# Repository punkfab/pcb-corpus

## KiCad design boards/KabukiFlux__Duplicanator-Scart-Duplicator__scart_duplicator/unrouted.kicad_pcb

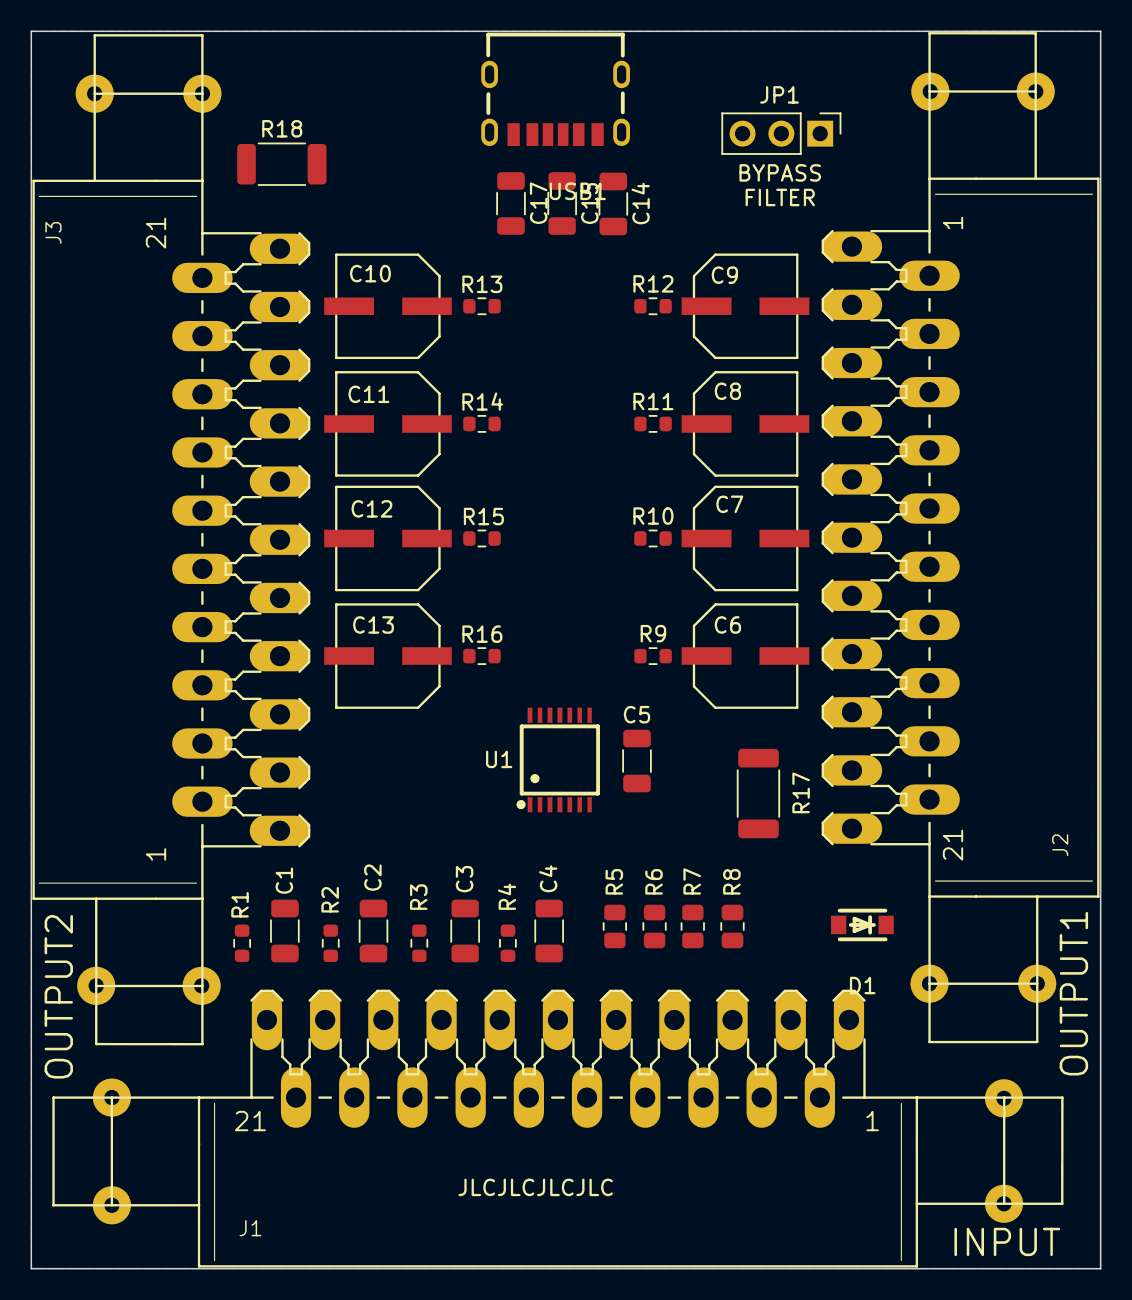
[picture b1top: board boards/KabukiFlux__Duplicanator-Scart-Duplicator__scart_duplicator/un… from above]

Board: 2 copper layers, 70.0 x 81.0 mm, 42 parts (1 on the bottom side), 38 nets, no tracks yet.

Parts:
C1, C2, C3, C4, C5, C17: 0.1u; C_1206_3216Metric
C6, C7, C8, C9, C10, C11, C12, C13: 330u; CAP-SMD_BD6.3-L6.6-W6.6-LS7.2-R-RD
C14: 10n; C_1206_3216Metric
C15: 10u; C_1206_3216Metric
D1: SOD4007; SOD-123F_L2.8-W1.8-LS3.7-RD
G1: LOGO; LogoKabuki
J1: INPUT; SCART-F_solder_pads
J2: OUTPUT1; SCART-F_solder_pads
J3: OUTPUT2; SCART-F_solder_pads
JP1: FILTER_BYPASS; PinHeader_1x03_P2.54mm_Vertical
R1, R2, R3, R4, R9, R10, R11, R12, R13, R14, R15, R16: 75; R_0603_1608Metric
R5, R6, R7, R8: 5.36M; R_0805_2012Metric
R17, R18: 180; R_2010_5025Metric
U1: THS7374IPWR; TSSOP-14_L5.0-W4.4-P0.65-LS6.5-BL
USB1: USB-312; USB-C-SMD_10P-P1.00-L6.8-W8.9

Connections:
+5V: C5.1, C14.1, C15.1, C17.1, JP1.3 (B), R5.2, R6.2, R7.2, R8.2, R17.2, R18.2, U1.10 (VS+), USB1.2 (B9_VBUS), USB1.5 (A9_VBUS)
/AUDIO_GND: J1.4, J2.4, J3.4
/AUDIO_LEFT: J1.6, J2.3, J3.3
/AUDIO_RIGHT: J1.2, J2.1, J3.1
/B_IN: C4.1, J1.7, R4.1
/B_OUT1: C9.2, J2.7
/B_OUT2: C13.2, J3.7
/CSYNC_IN: C1.1, J1.20, R1.1
/CSYNC_OUT1: C6.2, J2.19
/CSYNC_OUT2: C10.2, J3.19
/G_IN: C3.1, J1.11, R3.1
/G_OUT1: C8.2, J2.11
/G_OUT2: C12.2, J3.11
/R_IN: C2.1, J1.15, R2.1
/R_OUT1: C7.2, J2.15
/R_OUT2: C11.2, J3.15
/SWITCHING: D1.1 (C), J2.8, J3.8
GND: C5.2, C14.2, C15.2, C17.2, J1.5, J1.9, J1.13, J1.17, J1.18, J1.21, J2.5, J2.9, J2.13, J2.17, J2.18, J2.21, J3.5, J3.9, J3.13, J3.17, J3.18, J3.21, JP1.1 (A), R1.2, R2.2, R3.2, R4.2, U1.5 (GND), U1.6 (DISABLE), USB1.0, USB1.1 (B12_GND), USB1.6 (A12_GND)
unnamed: C6.1, R9.2
unnamed: C7.1, R10.2
unnamed: C8.1, R11.2
unnamed: C9.1, R12.2
unnamed: C10.1, R13.2
unnamed: C11.1, R14.2
unnamed: C12.1, R15.2
unnamed: C13.1, R16.2
unnamed: D1.2 (A), J1.8
unnamed: J2.16, R17.1
unnamed: J3.16, R18.1
unnamed: JP1.2 (C), U1.9 (BYPASS)
unnamed: C1.2, R5.1, U1.1 (CH1IN)
unnamed: R9.1, R13.1, U1.14 (CH1OUT)
unnamed: C2.2, R6.1, U1.2 (CH2IN)
unnamed: R10.1, R14.1, U1.13 (CH2OUT)
unnamed: C3.2, R7.1, U1.3 (CH3IN)
unnamed: R11.1, R15.1, U1.12 (CH3OUT)
unnamed: C4.2, R8.1, U1.4 (CH4IN)
unnamed: R12.1, R16.1, U1.11 (CH4OUT)

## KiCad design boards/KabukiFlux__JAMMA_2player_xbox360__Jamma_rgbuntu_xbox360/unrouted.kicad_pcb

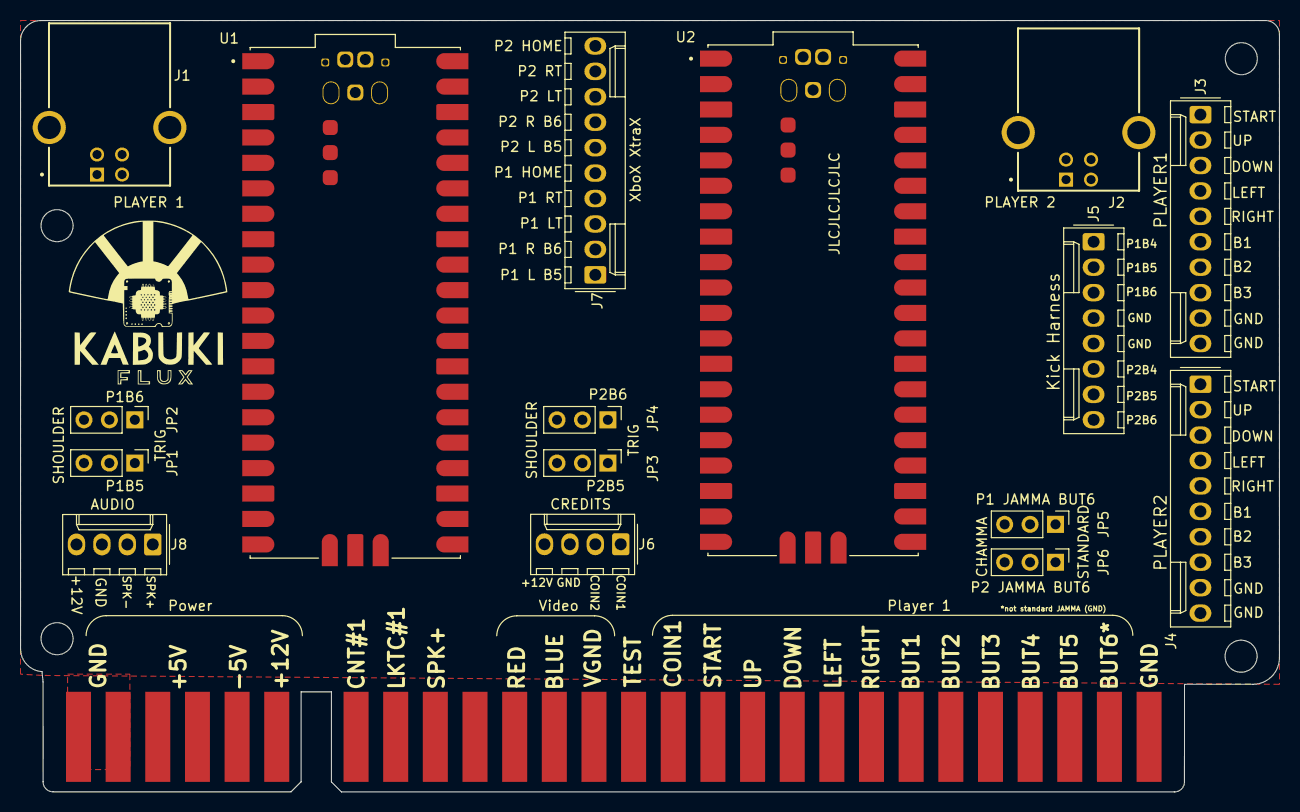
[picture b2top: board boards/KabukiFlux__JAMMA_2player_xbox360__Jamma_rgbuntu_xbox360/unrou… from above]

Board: 2 copper layers, 125.7 x 77.0 mm, 22 parts (0 on the bottom side), 47 nets, no tracks yet.

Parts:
G1: LOGO; LogoKabuki_18mm
HOLE1, HOLE2, HOLE3, HOLE4: MountingHole_3.2mm_M3
J1: USB-B PICO1; USB-B
J2: USB-B PICO2; USB-B
J3: PLAYER1; Molex_KK-254_AE-6410-10A_1x10_P2.54mm_Vertical
J4: PLAYER2; Molex_KK-254_AE-6410-10A_1x10_P2.54mm_Vertical
J5: Kick Harness; Molex_KK-254_AE-6410-08A_1x08_P2.54mm_Vertical
J6: CREDITS; Molex_KK-254_AE-6410-04A_1x04_P2.54mm_Vertical
J7: XboX XtraX; Molex_KK-254_AE-6410-10A_1x10_P2.54mm_Vertical
J8: AUDIO; Molex_KK-254_AE-6410-04A_1x04_P2.54mm_Vertical
J9: JAMMA_edge_conn; JAMMA_edge
JP1: P1_B5_SELECTOR; PinHeader_1x03_P2.54mm_Vertical
JP2: P1_B6_SELECTOR; PinHeader_1x03_P2.54mm_Vertical
JP3: P2_B5_SELECTOR; PinHeader_1x03_P2.54mm_Vertical
JP4: P2_B6_SELECTOR; PinHeader_1x03_P2.54mm_Vertical
JP5: P1 JAMMA BUT6; PinHeader_1x03_P2.54mm_Vertical
JP6: P2 JAMMA BUT6; PinHeader_1x03_P2.54mm_Vertical
U1, U2: pi_pico; pi-pico

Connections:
/+12V: J6.4, J8.4, J9.6 (+12V), J9.F (+12V)
/GND: J1.4 (GND), J2.4 (GND), J3.9, J3.10, J4.9, J4.10, J5.4, J5.5, J6.3, J8.3, J9.1 (GND), J9.2 (GND), J9.28 (GND), J9.A (GND), J9.B (GND), J9.f (GND), JP5.1 (A), JP6.1 (A), U1.3 (GND), U1.8 (GND), U1.13 (GND), U1.18 (GND), U1.23 (GND), U1.28 (GND), U1.38 (GND), U1.D2 (GND), U1.TP1 (TP1_GND), U2.3 (GND), U2.8 (GND), U2.13 (GND), U2.18 (GND), U2.23 (GND), U2.28 (GND), U2.38 (GND), U2.D2 (GND), U2.TP1 (TP1_GND)
/P1_A_B1: J3.6, J9.22 (Player_1_Button_1), U1.9 (GP6)
/P1_B5: J5.2, J9.26 (Unused), JP1.2 (C)
/P1_B6: J5.3, JP2.2 (C), JP5.3 (B)
/P1_B_B2: J3.7, J9.23 (Player_1_Button_2), U1.10 (GP7)
/P1_COIN_B7: J6.1, J9.16 (Coin_1), U1.21 (GP16)
/P1_DPAD_DOWN: J3.3, J9.19 (Player_1_Down), U1.5 (GP3)
/P1_DPAD_LEFT: J3.4, J9.20 (Player_1_Left), U1.7 (GP5)
/P1_DPAD_RIGHT: J3.5, J9.21 (Player_1_Right), U1.6 (GP4)
/P1_DPAD_UP: J3.2, J9.18 (Player_1_Up), U1.4 (GP2)
/P1_HOME: J7.5, U1.26 (GP20)
/P1_JAMMA_B6_GND: J9.27 (GND), JP5.2 (C)
/P1_LT: J7.3, JP1.1 (A), U1.12 (GP9)
/P1_L_B5: J7.1, JP1.3 (B), U1.17 (GP13)
/P1_RT: J7.4, JP2.1 (A), U1.11 (GP8)
/P1_R_B6: J7.2, JP2.3 (B), U1.16 (GP12)
/P1_START_B8: J3.1, J9.17 (Player_1_Start), U1.22 (GP17)
/P1_X_B3: J3.8, J9.24 (Player_1_Button_3), U1.14 (GP10)
/P1_Y_B4: J5.1, J9.25 (Player_1_Button_4), U1.15 (GP11)
/P2_A_B1: J4.6, J9.Z (Player_2_Button_1), U2.9 (GP6)
/P2_B5: J5.7, J9.d (Unused), JP3.2 (C)
/P2_B6: J5.8, JP4.2 (C), JP6.3 (B)
/P2_B_B2: J4.7, J9.a (Player_2_Button_2), U2.10 (GP7)
/P2_COIN_B7: J6.2, J9.T (Coin_2), U2.21 (GP16)
/P2_DPAD_DOWN: J4.3, J9.W (Player_2_Down), U2.5 (GP3)
/P2_DPAD_LEFT: J4.4, J9.X (Player_2_Left), U2.7 (GP5)
/P2_DPAD_RIGHT: J4.5, J9.Y (Player_2_Right), U2.6 (GP4)
/P2_DPAD_UP: J4.2, J9.V (Player_2_Up), U2.4 (GP2)
/P2_HOME: J7.10, U2.26 (GP20)
/P2_JAMMA_B6_GND: J9.e (GND), JP6.2 (C)
/P2_LT: J7.8, JP3.1 (A), U2.12 (GP9)
/P2_L_B5: J7.6, JP3.3 (B), U2.17 (GP13)
/P2_RT: J7.9, JP4.1 (A), U2.11 (GP8)
/P2_R_B6: J7.7, JP4.3 (B), U2.16 (GP12)
/P2_START_B8: J4.1, J9.U (Player_2_Start), U2.22 (GP17)
/P2_X_B3: J4.8, J9.b (Player_2_Button_3), U2.14 (GP10)
/P2_Y_B4: J5.6, J9.c (Player_2_Button_4), U2.15 (GP11)
/PICO1_D+: J1.3 (D+), U1.TP3 (TP3_USB_DP)
/PICO1_D-: J1.2 (D-), U1.TP2 (TP2_USB_DM)
/PICO2_D+: J2.3 (D+), U2.TP3 (TP3_USB_DP)
/PICO2_D-: J2.2 (D-), U2.TP2 (TP2_USB_DM)
/SPK+: J8.1, J9.10 (Speaker+)
/SPK-: J8.2, J9.L (Speaker-)
/USB_PICO1_VCC: J1.1 (VCC), U1.40 (VBUS)
/USB_PICO2_VCC: J2.1 (VCC), U2.40 (VBUS)
/USB_SHIELD: J1.S1 (SHIELD), J1.S2 (SHIELD), J2.S1 (SHIELD), J2.S2 (SHIELD), U1.A (USB_SHIELD), U1.B (USB_SHIELD), U1.C (USB_SHIELD), U1.D (USB_SHIELD), U2.A (USB_SHIELD), U2.B (USB_SHIELD), U2.C (USB_SHIELD), U2.D (USB_SHIELD)

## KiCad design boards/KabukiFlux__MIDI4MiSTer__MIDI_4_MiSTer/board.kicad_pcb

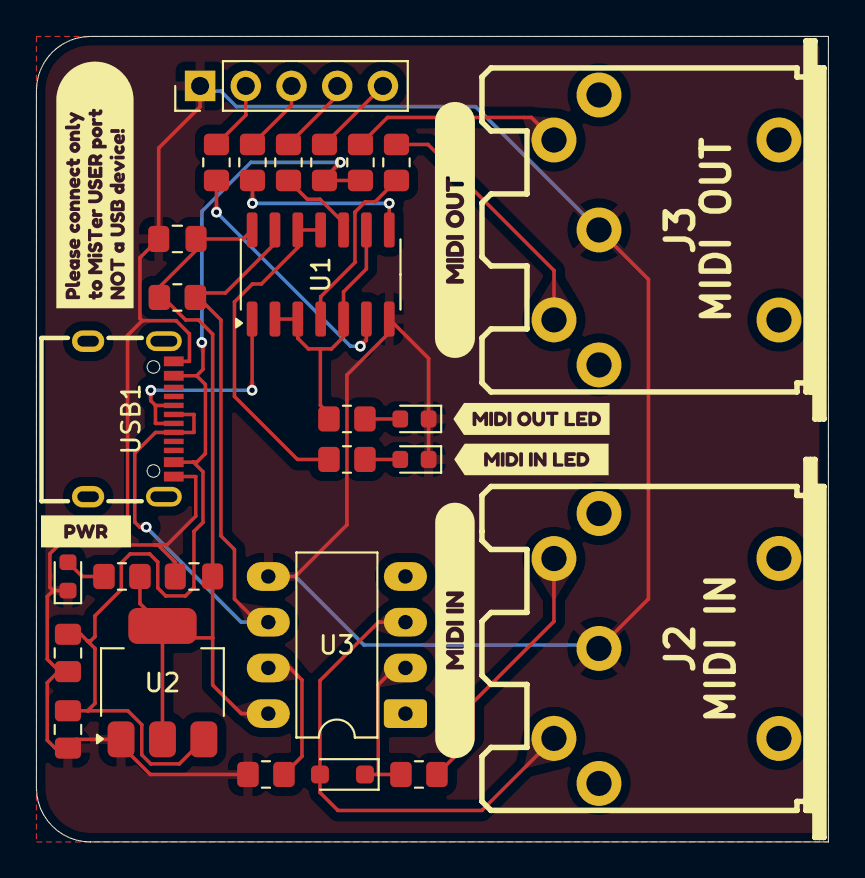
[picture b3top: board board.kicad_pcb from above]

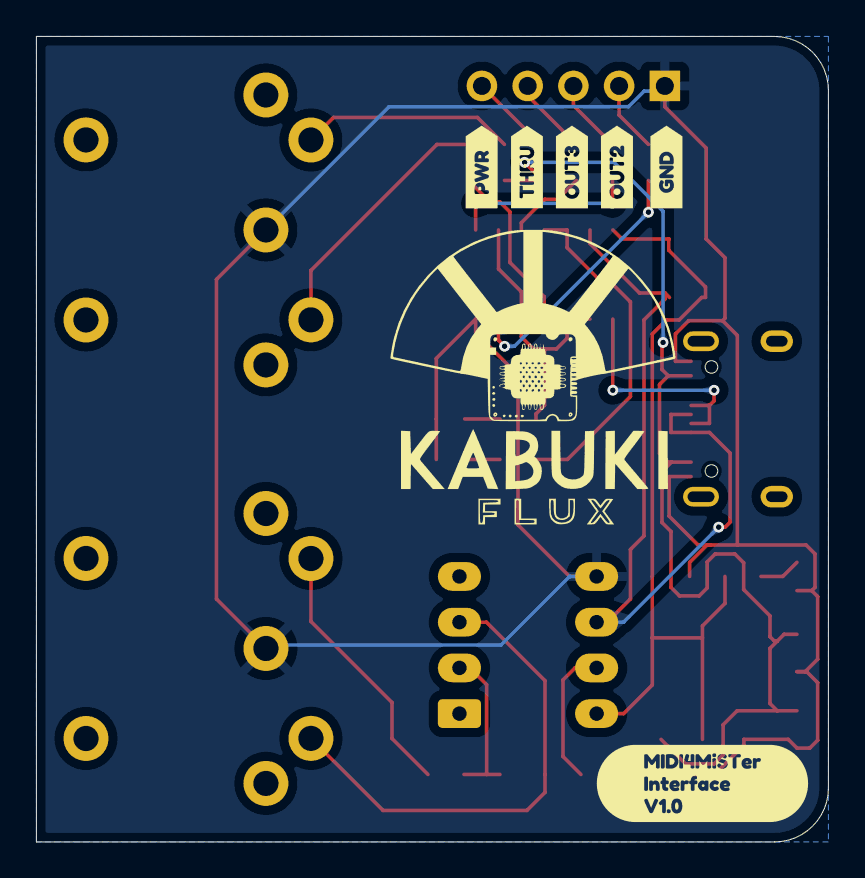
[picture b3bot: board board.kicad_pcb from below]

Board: 2 copper layers, 44.0 x 44.8 mm, 40 parts (7 on the bottom side), 24 nets.

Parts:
C1, C4: 0.1uF; C_0805_2012Metric_Pad1.18x1.45mm_HandSolder
C2, C3: 1uF; C_0805_2012Metric_Pad1.18x1.45mm_HandSolder
D1: POWER_LED; LED_0603_1608Metric
D2: 1N4148; D_SOD-323_HandSoldering
D3: MIDI_OUT_LED; LED_0603_1608Metric
D4: MIDI_IN_LED; LED_0603_1608Metric
G01: LOGO; LogoKabuki_18mm
J2: MIDI IN; MIDI_DIN5
J3: MIDI OUT; MIDI_DIN5
J4: MIDI_EXTRAS; PinHeader_1x05_P2.54mm_Vertical
R1, R4, R5, R6, R7, R8, R9, R11, R12: 220; R_0805_2012Metric_Pad1.20x1.40mm_HandSolder
R2: 10k; R_0805_2012Metric_Pad1.20x1.40mm_HandSolder
R3: 2k2; R_0805_2012Metric_Pad1.20x1.40mm_HandSolder
R10: 100; R_0805_2012Metric_Pad1.20x1.40mm_HandSolder
U1: 74HC14; SOIC-14_3.9x8.7mm_P1.27mm
U2: AMS1117; SOT-223-3_TabPin2
U3: 6N138; DIP-8_W7.62mm_LongPads
USB1: TYPE-C 16PIN 2MD(073); USB-C-SMD_TYPE-C-6PIN-2MD-073
kibuzzard-67F911EE: G***; kibuzzard-67F911EE
kibuzzard-67F911FC: G***; kibuzzard-67F911FC
kibuzzard-67F912C1: G***; kibuzzard-67F912C1
kibuzzard-67F9106B: G***; kibuzzard-67F9106B
kibuzzard-67F9113A: G***; kibuzzard-67F9113A
kibuzzard-67F91050: G***; kibuzzard-67F91050
kibuzzard-67F91059: G***; kibuzzard-67F91059
kibuzzard-67F91062: G***; kibuzzard-67F91062
kibuzzard-67F91074: G***; kibuzzard-67F91074
kibuzzard-67F91142: G***; kibuzzard-67F91142
kibuzzard-67F91168: G***; kibuzzard-67F91168
kibuzzard-67F91733: G***; kibuzzard-67F91733

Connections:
/+3V3: C3.1, C4.1, R1.1, R2.2, U1.14 (VCC), U2.2 (VO), U3.8 (VCC)
/+5V: C1.1, C2.1, R11.2, R12.2, U2.3 (VI), USB1.2 (VBUS), USB1.11 (VBUS)
/GND: C1.2, C2.2, C3.2, C4.2, D1.1 (K), D3.1 (K), D4.1 (K), J2.2, J3.2, J4.1, R3.2, U1.7 (GND), U2.1 (ADJ), U3.5 (GND), USB1.1 (GND), USB1.12 (GND)
/MIDI_IN_1: J2.4, R10.1
/MIDI_IN_1_SINK: D2.2 (A), J2.5, U3.3 (C2)
/MIDI_OUT_1: J3.5, R5.2
/MIDI_OUT_2: J4.2, R6.2
/MIDI_OUT_3: J4.3, R7.2
/MIDI_PWR: J4.5, R12.1
/MIDI_THRU: J4.4, R8.2
/MiSTer_USR_MIDI_IN: R2.1, U1.13, U3.6 (VO2), USB1.6 (DP1), USB1.8 (DP2)
/MiSTer_USR_MIDI_OUT: U1.1, USB1.5 (DN2), USB1.7 (DN1)
/PWR_OUT_1: J3.4, R11.1
unnamed: D1.2 (A), R1.2
unnamed: D2.1 (K), R10.2, U3.2 (C1)
unnamed: D3.2 (A), R4.2
unnamed: D4.2 (A), R9.2
unnamed: R4.1, U1.2, U1.3, U1.5, U1.9
unnamed: R5.1, U1.4
unnamed: R6.1, U1.6
unnamed: R7.1, U1.8
unnamed: R8.1, U1.10
unnamed: R9.1, U1.11, U1.12
unnamed: R3.1, U3.7 (VO1)

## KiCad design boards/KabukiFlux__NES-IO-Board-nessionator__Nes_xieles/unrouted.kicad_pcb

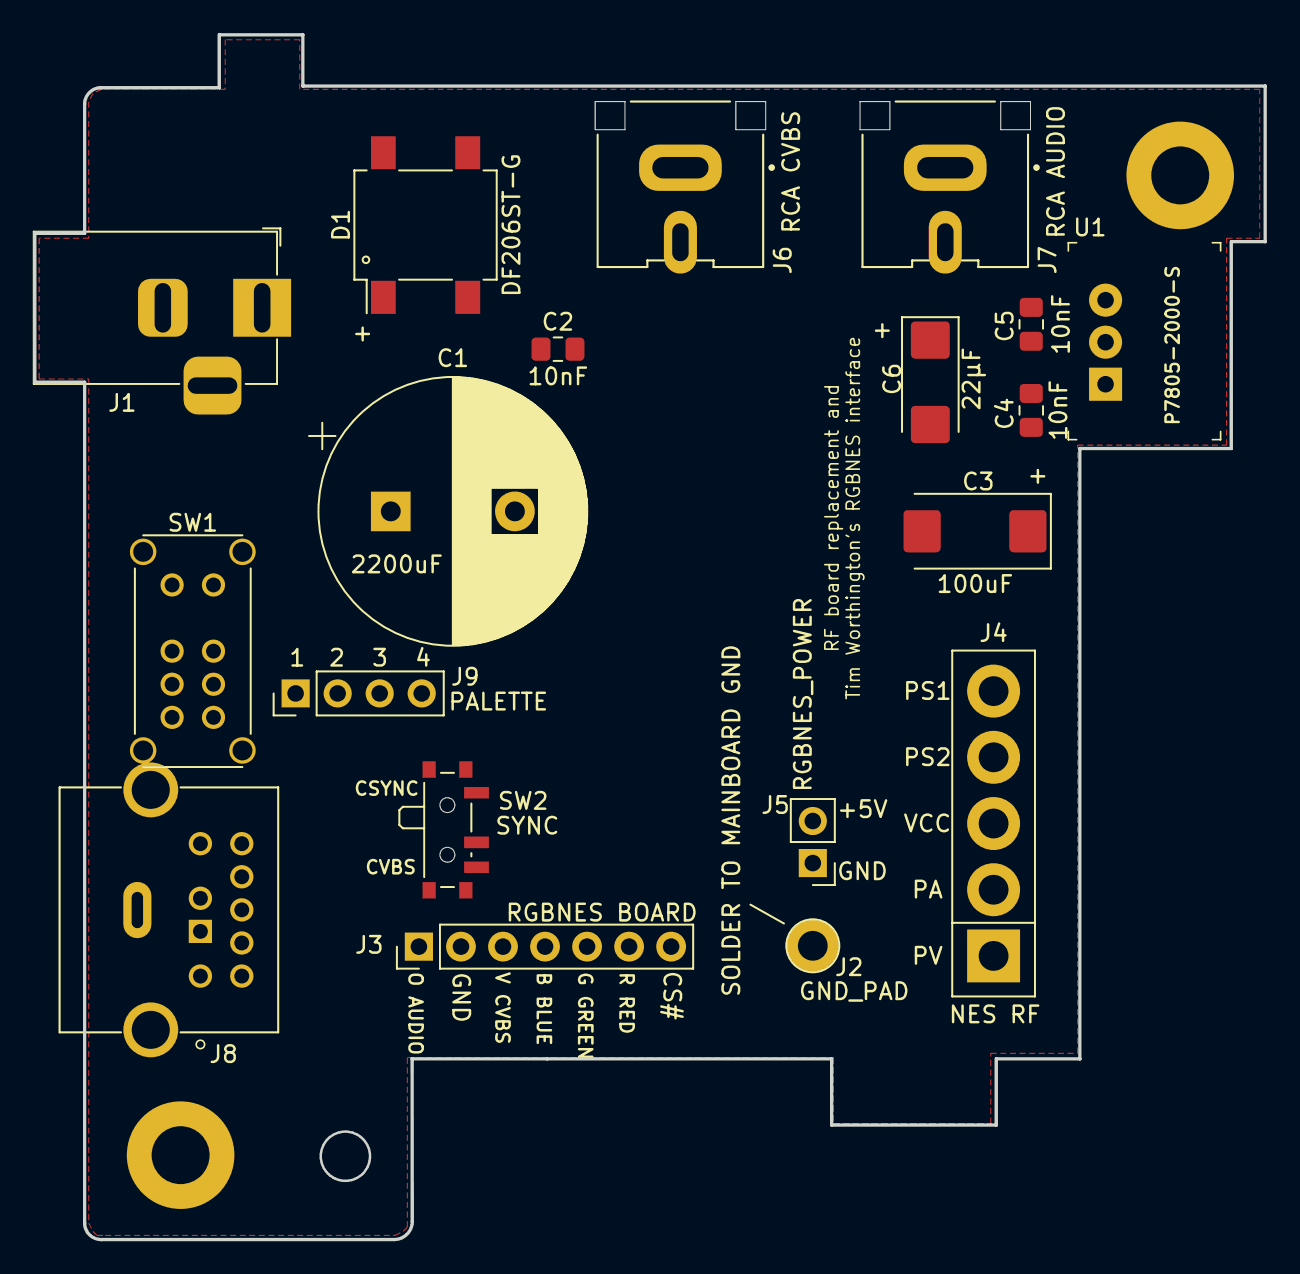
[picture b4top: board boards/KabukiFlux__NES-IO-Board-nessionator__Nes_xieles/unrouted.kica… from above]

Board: 2 copper layers, 74.3 x 72.8 mm, 21 parts (0 on the bottom side), 17 nets, no tracks yet.

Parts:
C1: 2200uF; CP_Radial_D16.0mm_P7.50mm
C2, C4, C5: 10nF; C_0805_2012Metric_Pad1.15x1.40mm_HandSolder
C3: 100uF; CP_EIA-7343-43_Kemet-X_Pad2.25x2.55mm_HandSolder
C6: 22μF; CP_EIA-6032-28_Kemet-C_Pad2.25x2.35mm_HandSolder
D1: DF206ST-G; Diode_Bridge_Vishay_DFS
J1: PJ-102BH; BarrelJack_NES
J2: GND_PAD; Pin_D1.3mm_L11.0mm
J3: Conn_NESRGB_TW; CONN_NESRGB_TW
J4: Conn_NES_RF; RF_CONN_NES
J5: RGBNES_POWER; PinHeader_1x02_P2.54mm_Vertical
J6: RCA CVBS; CUI_RCJ-043
J7: RCA AUDIO; CUI_RCJ-043
J8: MD-90SM; CUI_MD-90SM
J9: Conn_Palette; PinHeader_1x04_P2.54mm_Vertical
MH1, MH2: MountingHole_3.5mm_Pad
SW1: EG2319
SW2: SYNC; SW_SPDT_PCM12
U1: P7805-2000-S; 3-SIP_Module_V7805-2000

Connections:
+5V: C5.1, C6.1, J4.3 (VCC), J5.2, J8.2 (5v), U1.3 (OUT)
/AC_PIN: D1.4, J1.1
/AC_SLEEVE: D1.3, J1.2, J1.3
/PALETTE_1: J9.1, SW1.5
/PALETTE_2: J9.2, SW1.7
/PALETTE_3: J9.3, SW1.8
/PALETTE_4: J9.4 (GND), SW1.6
AUDIO_MONO: J3.1 (AUDIO_O), J7.1 (In), J8.6 (A_MONO), J8.8 (A_LEFT), J8.9 (A_RIGHT)
BLUE: J3.4 (BLUE_B), J8.1 (BLUE)
CS#SYNC: J3.7 (SYNC_CS#), J8.5 (SYNC), SW2.1 (A)
CVBS: J3.3 (CVBS_V), J6.1 (In), SW2.3 (C)
GND: C1.2, C2.2, C3.2, C4.2, C5.2, C6.2, D1.2 (-), J2.1, J3.2 (GND), J5.1, J6.2 (Ext), J7.2 (Ext), J8.S1 (SHIELD), J8.S2 (SHIELD), J8.S3 (SHIELD), U1.2 (GND)
GREEN: J3.5 (GREEN_G), J8.3 (GREEN)
PS1: C1.1, C2.1, D1.1 (+), J4.5 (PS1)
PS2: C3.1, C4.1, J4.4 (PS2), U1.1 (IN)
RED: J3.6 (RED_R), J8.7 (RED)
SCART_SYNC: J8.4 (CVBS), SW2.2 (B)

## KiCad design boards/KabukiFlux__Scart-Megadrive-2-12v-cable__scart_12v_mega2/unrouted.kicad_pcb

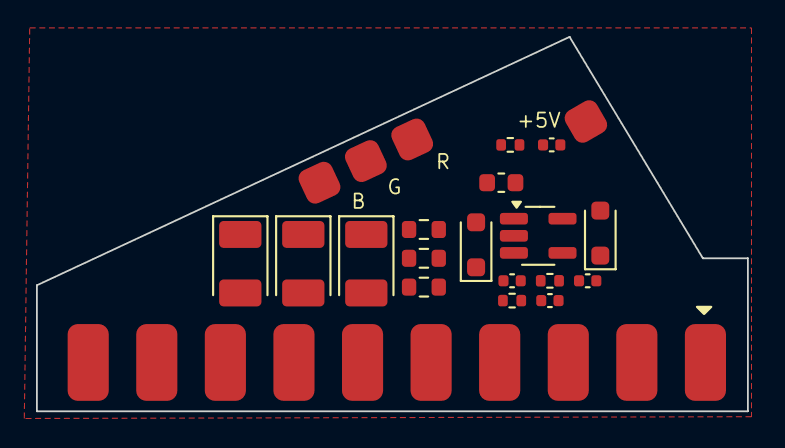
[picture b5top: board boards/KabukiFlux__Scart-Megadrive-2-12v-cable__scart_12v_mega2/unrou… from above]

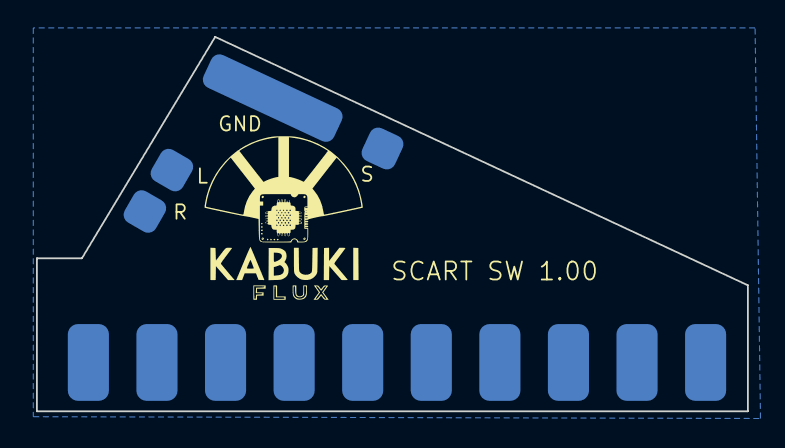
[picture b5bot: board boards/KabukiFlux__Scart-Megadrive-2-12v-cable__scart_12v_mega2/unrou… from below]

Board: 2 copper layers, 39.5 x 20.8 mm, 27 parts (5 on the bottom side), 19 nets, no tracks yet.

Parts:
C1: 100nF; C_0402_1005Metric
C2: 4.7uF; C_0402_1005Metric
C3: 10pF; C_0402_1005Metric
C4: 1uF; C_0402_1005Metric
CB1: 220uF; CP_EIA-3528-21_Kemet-B_Pad1.50x2.35mm_HandSolder
CG1: 220uF; CP_EIA-3528-21_Kemet-B_Pad1.50x2.35mm_HandSolder
CR1: 220uF; CP_EIA-3528-21_Kemet-B_Pad1.50x2.35mm_HandSolder
D1, D2: D_Schottky; D_SOD-323_HandSoldering
G1: LOGO; LogoKabuki_10mm
J1, J2, J3, J4, J5, J6, J7: Conn_01x01; PAD2x2mm
J8: Conn_01x01; PAD2x8mm
L1: 10uH; L_0603_1608Metric
R1: 1.6M; R_0402_1005Metric
R2: 200K; R_0402_1005Metric
R3: 180; R_0402_1005Metric
RB1: 75; R_0603_1608Metric
RG1: 75; R_0603_1608Metric
RR1: 75; R_0603_1608Metric
S1: SCART MALE; SCART
U1: TPS61040DBVR; SOT-23-5_HandSoldering

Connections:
+5V: C1.1, D1.2 (A), J7.1, R3.2
/AUDIO_LEFT: J6.1, S1.6
/AUDIO_RIGHT: J5.1, S1.2
/BLUE: J3.1, RB1.1
/BLUE_SC: CB1.2, S1.7
/GREEN: J2.1, RG1.1
/GREEN_SC: CG1.2, S1.11
/RED: J1.1, RR1.1
/RED_SC: CR1.2, S1.15
/SWITCHING: C3.1, C4.1, D2.1 (K), R1.1, S1.8
/SYNC: J4.1, S1.20
GND: C1.2, C2.2, C4.2, J8.1, R2.2, S1.4, S1.5, S1.9, S1.13, S1.17, S1.18, U1.2 (GND)
unnamed: CB1.1, RB1.2
unnamed: CG1.1, RG1.2
unnamed: CR1.1, RR1.2
unnamed: C2.1, D1.1 (K), L1.1, U1.4 (EN), U1.5 (VIN)
unnamed: D2.2 (A), L1.2, U1.1 (SW)
unnamed: R3.1, S1.16
unnamed: C3.2, R1.2, R2.1, U1.3 (FB)

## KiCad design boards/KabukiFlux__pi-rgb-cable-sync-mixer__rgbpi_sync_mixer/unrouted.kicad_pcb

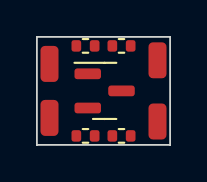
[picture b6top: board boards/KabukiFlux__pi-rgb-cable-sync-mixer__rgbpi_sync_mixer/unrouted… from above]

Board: 2 copper layers, 7.4 x 6.0 mm, 9 parts (0 on the bottom side), 7 nets, no tracks yet.

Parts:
CSYNC1: CSYNC CONN; SolderWirePad_1x01_SMD_1x2mm
GND1: GND CONN; SolderWirePad_1x01_SMD_1x2mm
HSYNC1: HSYNC CONN; SolderWirePad_1x01_SMD_1x2mm
Q1: MMBT3904; SOT-23
R1: 100; R_0402_1005Metric
R2: 10k; R_0402_1005Metric
R3: 1k; R_0402_1005Metric
R4: 470; R_0402_1005Metric
VSYNC1: VSYNC CONN; SolderWirePad_1x01_SMD_1x2mm

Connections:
/CSYNC: CSYNC1.1, R4.2
/HSYNC: HSYNC1.1, R2.1
/VSYNC: R1.1, VSYNC1.1
GND: GND1.1, R3.2
unnamed: Q1.1 (B), R2.2
unnamed: Q1.3 (C), R1.2
unnamed: Q1.2 (E), R3.1, R4.1

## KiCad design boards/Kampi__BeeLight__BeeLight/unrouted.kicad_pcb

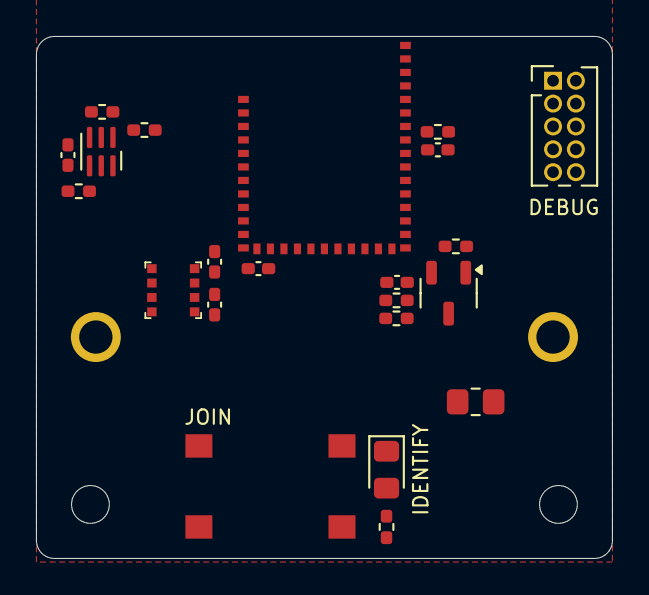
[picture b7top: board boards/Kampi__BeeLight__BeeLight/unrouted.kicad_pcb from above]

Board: 2 copper layers, 32.0 x 29.0 mm, 23 parts (1 on the bottom side), 15 nets, no tracks yet.

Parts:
BT101: Battery_Cell; 3039
C101, C102, C104, C105, C106: 100n; C_0402_1005Metric_Pad0.74x0.62mm_HandSolder
C103: 1n; C_0402_1005Metric_Pad0.74x0.62mm_HandSolder
D101: IDENTIFY; LED_0805_2012Metric_Pad1.15x1.40mm_HandSolder
IC102: APDS-9306-065; Broadcom_DFN-6_2x2mm_P0.65mm
IC103: BME688; Bosch_LGA-8_3x3mm_P0.8mm_ClockwisePinNumbering
M101: BL54L15
Q101: BSS84; SOT-23-3
R101, R107: 100k; R_0402_1005Metric_Pad0.72x0.64mm_HandSolder
R102: 0R; R_0805_2012Metric_Pad1.20x1.40mm_HandSolder
R103: 220R; R_0402_1005Metric_Pad0.72x0.64mm_HandSolder
R104, R105, R106: 1k8; R_0402_1005Metric_Pad0.72x0.64mm_HandSolder
R108: 8k2; R_0402_1005Metric_Pad0.72x0.64mm_HandSolder
R109: 2k2; R_0402_1005Metric_Pad0.72x0.64mm_HandSolder
SW101: JOIN; WS-TASV-6x6
X102: DEBUG; PinHeader_2x05_P1.27mm_Vertical

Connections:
+BATT: C102.1, C104.1, C105.1, C106.1, IC102.3 (VDD), IC103.2 (CSB), IC103.6 (VDDIO), IC103.8 (VDD), M101.26 (VDD), Q101.2 (S), R101.1, R102.2, R103.1, R104.1, R105.1, R106.1, R107.1, X102.1 (VTref)
Enable-Battery: M101.11 (P2.04), Q101.1 (G), R107.2
GND: BT101.2 (-), C101.2, C102.2, C103.2, C104.2, C105.2, C106.2, IC102.6 (GND), IC103.1 (GND), IC103.5 (SDO), IC103.7 (GND), M101.1 (GND), M101.16 (GND), M101.27 (GND), M101.39 (GND), R109.2, SW101.1, X102.3 (GND), X102.5 (GND)
INT: IC102.4 (INT), M101.32 (P1.14/AIN7), R106.2
unnamed: BT101.1 (+), R102.1
unnamed: D101.2 (A), R103.2
unnamed: D101.1 (K), M101.24 (P1.01/32K)
unnamed: M101.25 (P1.00/32K), SW101.2
unnamed: Q101.3 (D), R108.1
SCL: IC102.1 (SCL), IC103.4 (SCK), M101.36 (P0.03), R105.2
SDA: IC102.2 (SDA), IC103.3 (SDI), M101.31 (P0.04), R104.2
SWDCLK: M101.6 (SWDCLK), X102.4 (SWCLK/TCK)
SWDIO: M101.5 (SWDIO), X102.2 (SWDIO/TMS)
V_{BAT}: C103.1, M101.23 (P1.04/AIN0), R108.2, R109.1
~RESET: C101.1, M101.7 (~RESET), R101.2, X102.10 (~RESET)
